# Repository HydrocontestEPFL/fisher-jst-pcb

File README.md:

# PCB for easier soldering

This PCB was made to distribute the mechanical load on all the pins at once.
Made for Fischer Ultimate series 07 3 pins, 5 pins, and 7 pins. Interface with JSP PA series connectors.

## This branch 

Here is an old design of the PCB. The holes for the Fischer side are inverted and not big enough.

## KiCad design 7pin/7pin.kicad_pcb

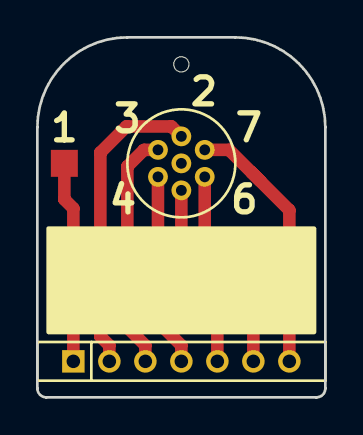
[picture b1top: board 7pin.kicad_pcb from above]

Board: 2 copper layers, 16.0 x 20.0 mm, 3 parts (0 on the bottom side), 7 nets.

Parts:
J1: Conn_01x01; Measurement_Point_Square-SMD-Pad_Small
J2: B07B-PASK-1(LF)(SN)
J3: UR01-07-7

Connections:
unnamed: J1.1, J2.1
unnamed: J2.2, J3.2
unnamed: J2.3, J3.3
unnamed: J2.4, J3.4
unnamed: J2.5, J3.5
unnamed: J2.6, J3.6
unnamed: J2.7, J3.7

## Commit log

2019-03-11 Add versions for 3, 5 and 7 contacts
2019-03-11 Add fabrication output
2019-03-18 Update output
2019-04-30 changing the size of the hole for the Fischer and pads type
2019-05-01 Flat cam preff
2019-05-01 Modif of gerber file for the pin 3 fischer
2019-05-01 Move config file for flatcam in robopoly's folder
2019-05-01 Update project
2019-05-02 Change design and foot print of the 5 pin, fabrication 3 pins near done
2019-05-02 Cleaning of the cam files
2019-05-02 5 pins fabrication project
2019-05-02 update and finish of the 5 pins project
2019-05-02 Drill all file for 5 pins
2019-05-03 Library update
2019-05-14 change in Layout
2019-05-14 README added
2019-05-14 Add readme
